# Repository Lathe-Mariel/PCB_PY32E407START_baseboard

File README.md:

KiCAD Project for Mother board of PY32E407_START(PUYA).

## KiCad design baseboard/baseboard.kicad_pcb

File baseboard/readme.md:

# BoM

型式 | 数量 | アイテム
---|---|---
FH-2x25SG(10) | 2 | 2.54連結ピンソケット
PH-2x5SG | 1 | 2.54ピンヘッダ
FH-2x2SG | 2 | 2.54ピンソケット
DTS-63-N-V-BLK | 1 | タクトスイッチ
 | 6 | Pmodソケット
OSR50603C1E | 4 | SMD LED
RC0603J220R | 4 | SMD 1608 220Ω
RK73B1JTTD103J | 4 | SMD 1608 10kΩ
TVBP06-B043CW-B | 4 | タクトスイッチ
ATA6561-GAQW-N | 1 | CANトランシーバ
SDCW3216-2-222TF | 1 | 表面実装用コモンモードチョークコイル
RC0603FR-0760R4L | 2 | SMD1608 60.4Ω
 | 1 | SMD1608 4.7nF
SM24CANB-02HTG | 1 | CAN TVS
 | 1 | CAN スクリューターミナル

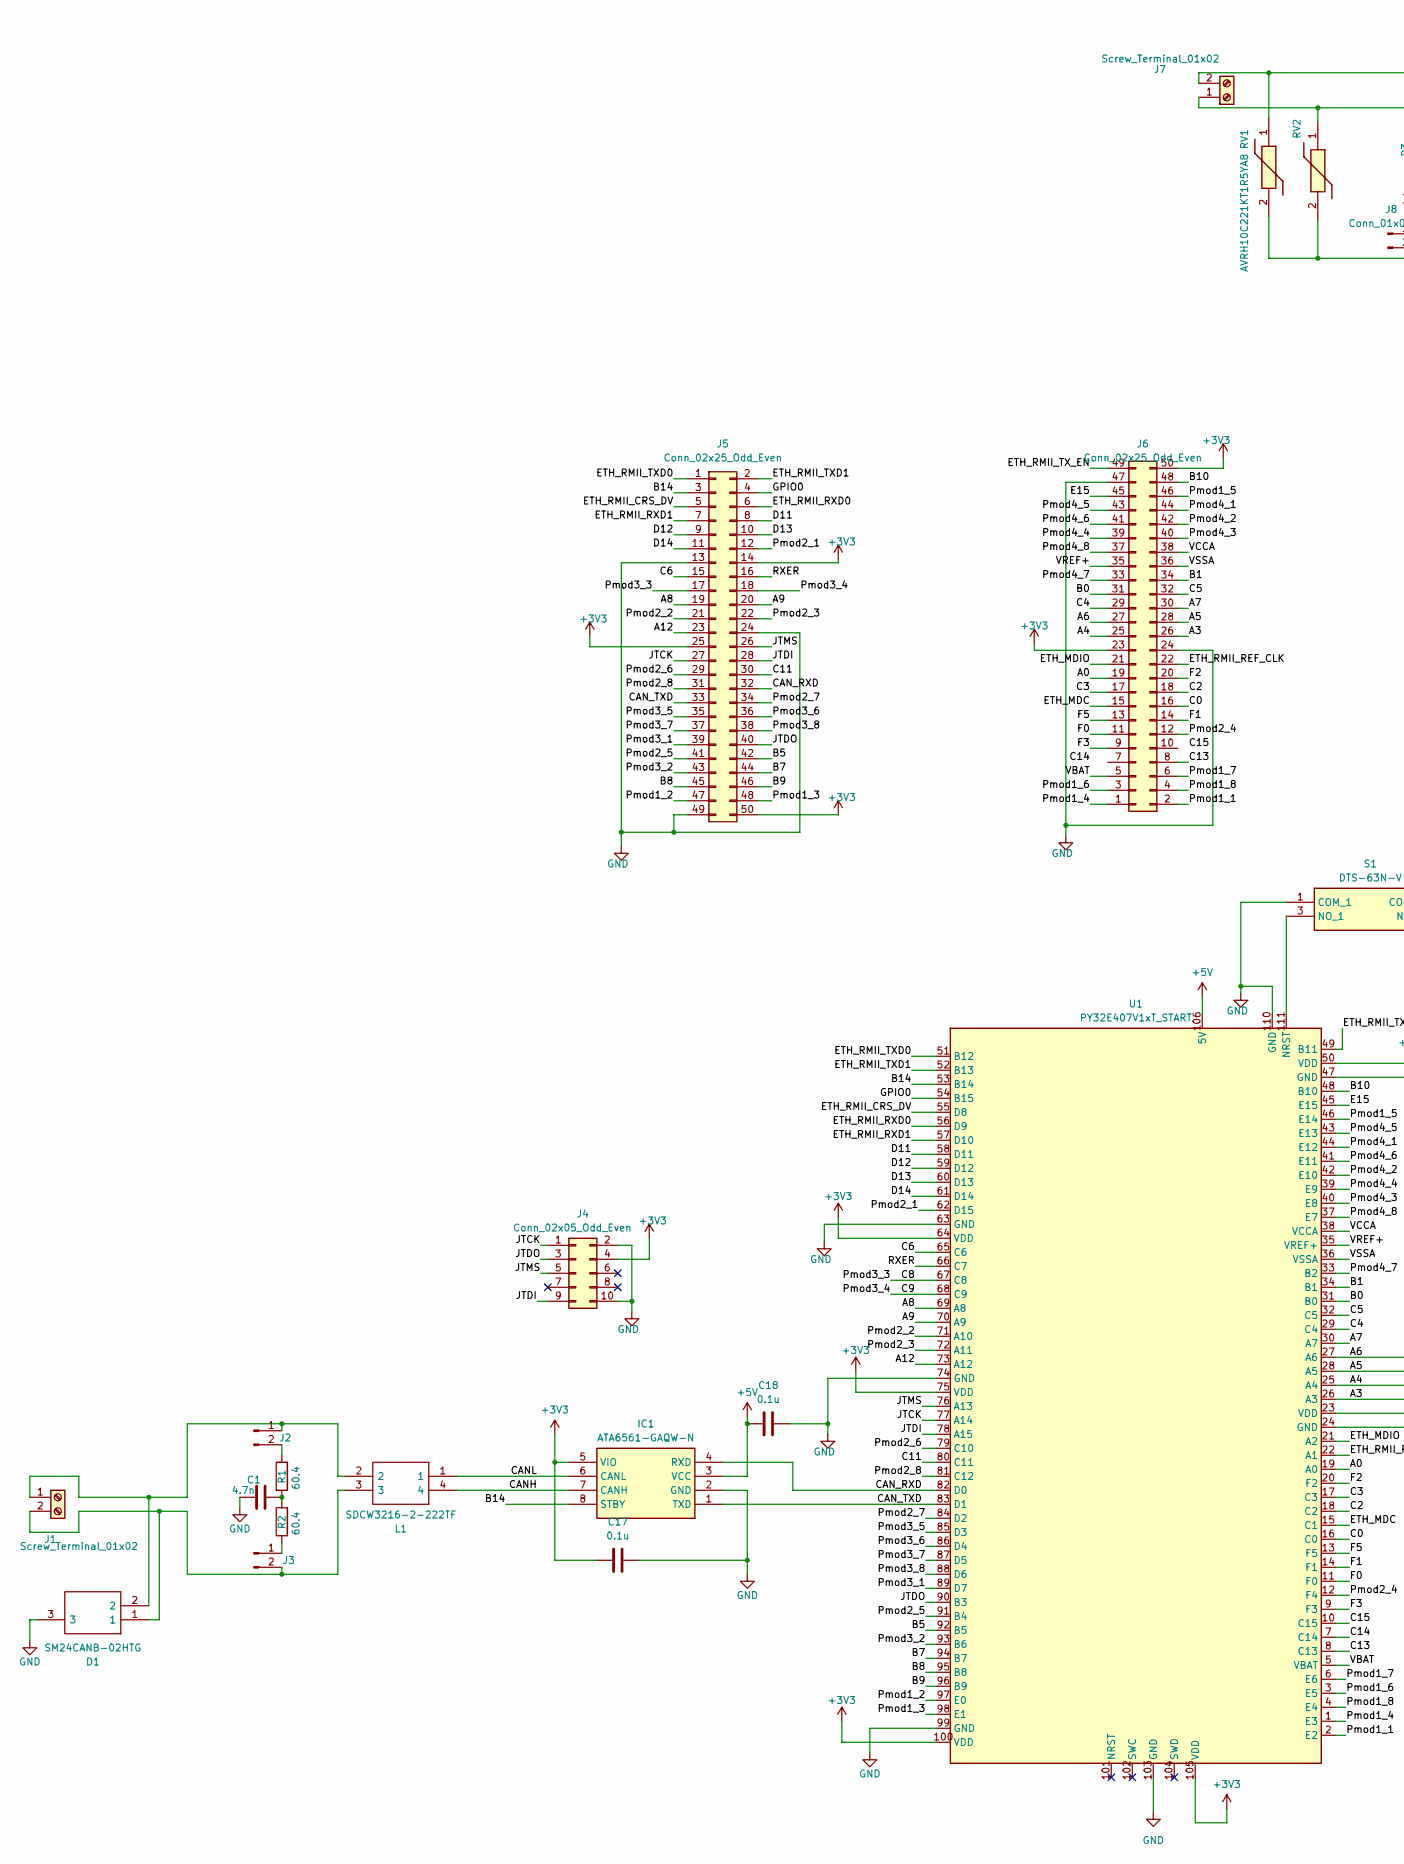
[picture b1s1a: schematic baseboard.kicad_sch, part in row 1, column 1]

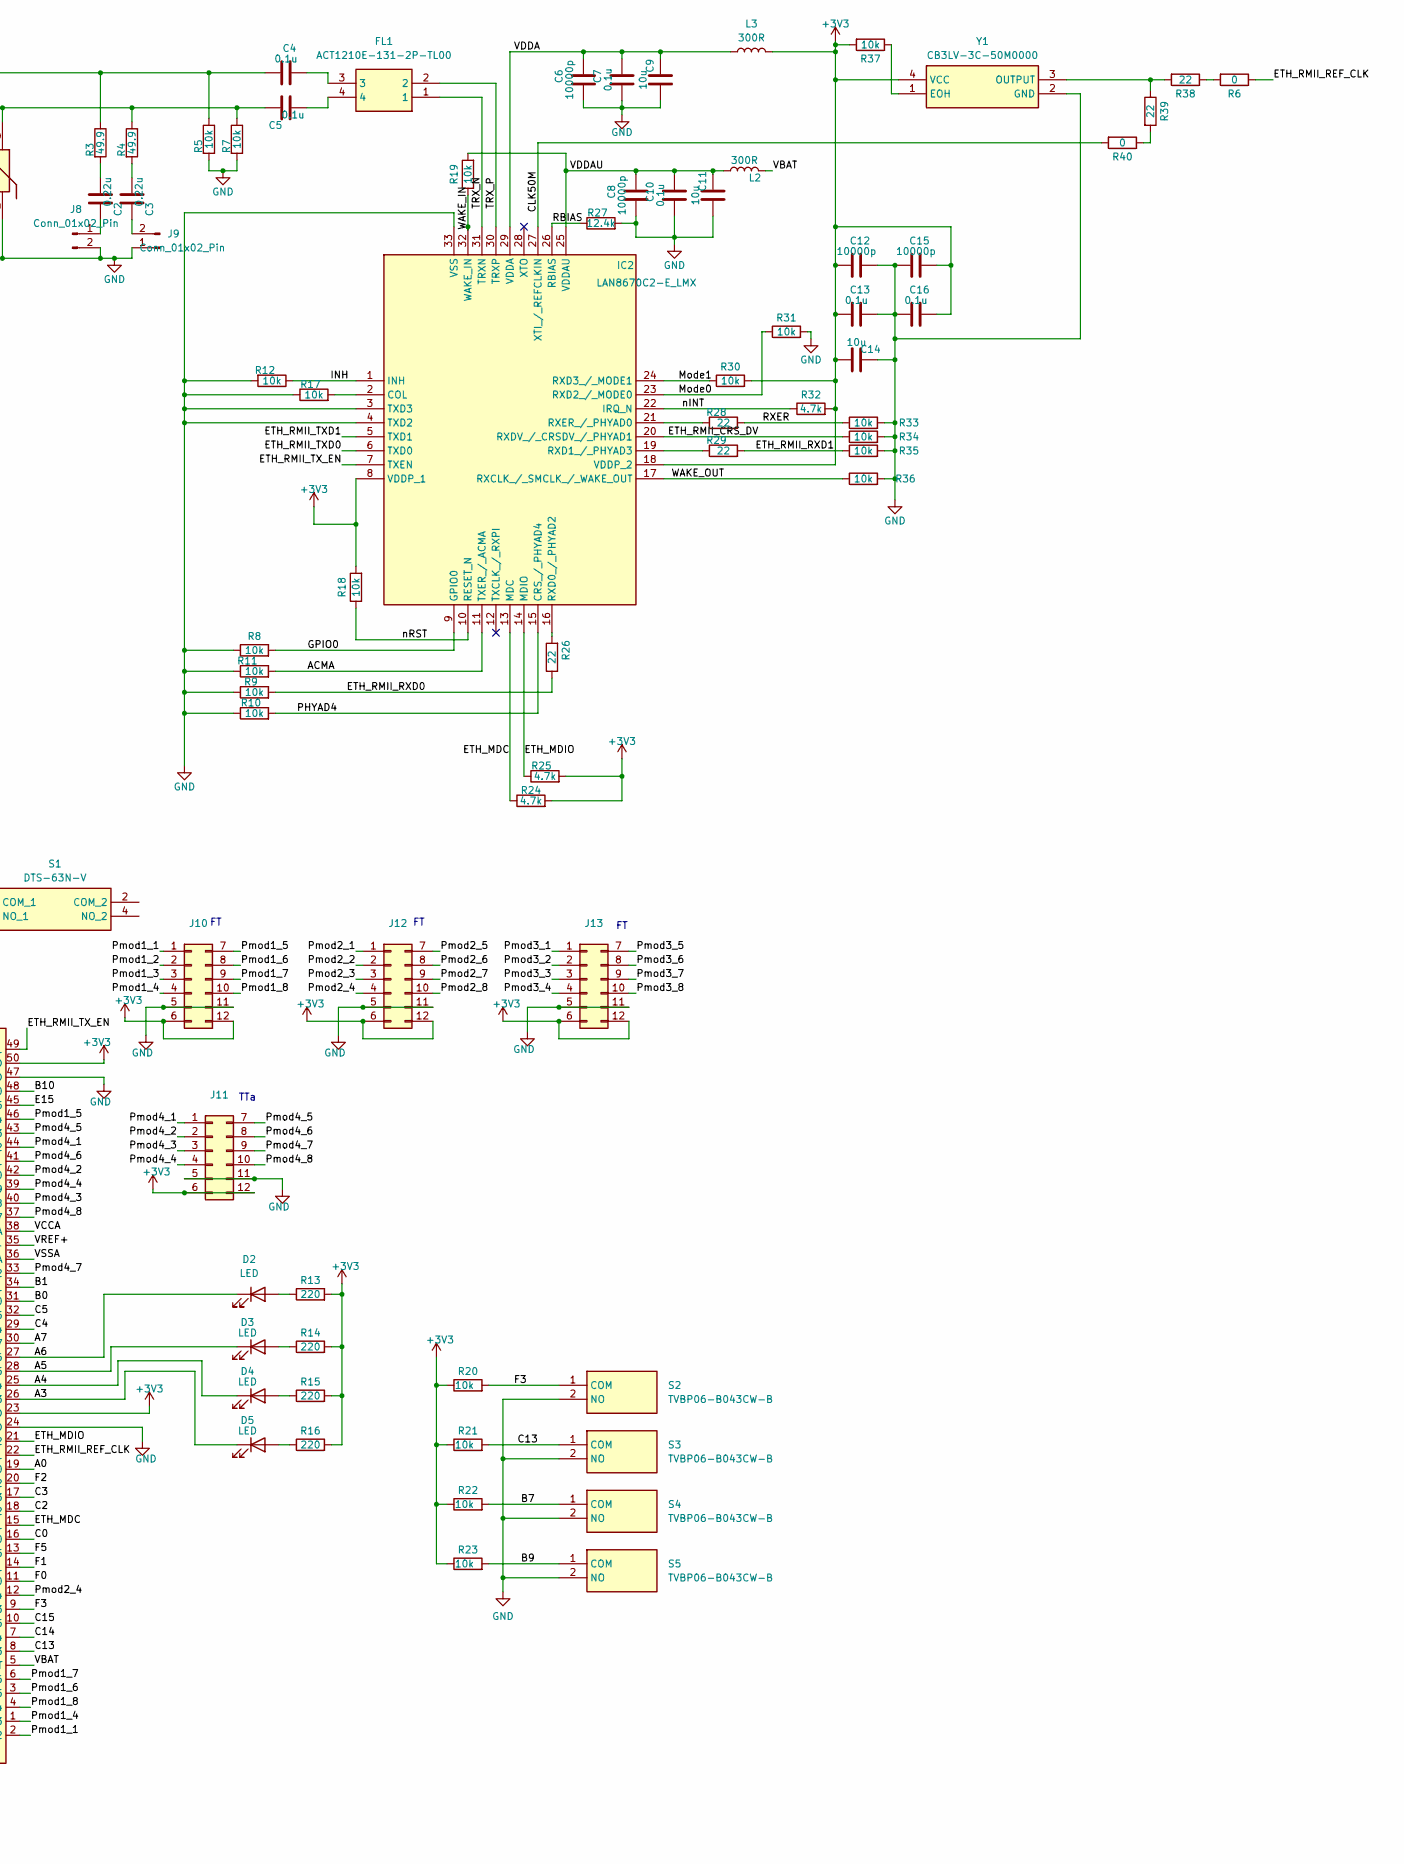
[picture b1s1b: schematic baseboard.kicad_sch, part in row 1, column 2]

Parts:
C1: 4.7n; C_0603_1608Metric_Pad1.08x0.95mm_HandSolder
C2, C3: 0.22u; C_0603_1608Metric_Pad1.08x0.95mm_HandSolder
C4, C5, C7, C10, C13, C16, C17, C18: 0.1u; C_0603_1608Metric_Pad1.08x0.95mm_HandSolder
C6, C8, C12, C15: 10000p; C_0603_1608Metric_Pad1.08x0.95mm_HandSolder
C9, C11, C14: 10u; C_0805_2012Metric_Pad1.18x1.45mm_HandSolder
D1: SM24CANB-02HTG; SM24CANB02HTG; Manufacturer_Part_Number SM24CANB-02HTG
D2, D3, D4, D5: LED; LED_0603_1608Metric_Pad1.05x0.95mm_HandSolder
FL1: ACT1210E-131-2P-TL00; ACT1210E1312PTL00; Manufacturer_Part_Number ACT1210E-131-2P-TL00
IC1: ATA6561-GAQW-N; SOIC127P600X175-8N; Manufacturer_Part_Number ATA6561-GAQW-N
IC2: LAN8670C2-E_LMX; QFN50P500X500X100-33N-D; Manufacturer_Part_Number LAN8670C2-E/LMX
J1: Screw_Terminal_01x02; TerminalBlock_Phoenix_MKDS-1,5-2-5.08_1x02_P5.08mm_Horizont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
J2, J3, J8, J9: Conn_01x02_Pin; PinHeader_1x02_P2.54mm_Vertical
J4: Conn_02x05_Odd_Even; PinHeader_2x05_P2.54mm_Vertical
J5, J6: Conn_02x25_Odd_Even; PinHeader_2x25_P2.54mm_Vertical
J7: Screw_Terminal_01x02; TerminalBlock_MetzConnect_Type055_RT01502HDWU_1x02_P5.00mm_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
J10, J11, J12, J13: Pmod_socket
L1: SDCW3216-2-222TF; SDCW32162222TF; Manufacturer_Part_Number SDCW3216-2-222TF
L2, L3: 300R; L_0603_1608Metric_Pad1.05x0.95mm_HandSolder
R1, R2: 60.4; R_0603_1608Metric_Pad0.98x0.95mm_HandSolder
R3, R4: 49.9; R_0603_1608Metric_Pad0.98x0.95mm_HandSolder
R5, R7, R8, R9, R10, R11, R12, R17, R18, R19, R20, R21, R22, R23, R30, R31, R33, R34, R35, R36, R37: 10k; R_0603_1608Metric_Pad0.98x0.95mm_HandSolder
R6, R40: 0; R_0603_1608Metric_Pad0.98x0.95mm_HandSolder
R13, R14, R15, R16: 220; R_0603_1608Metric_Pad0.98x0.95mm_HandSolder
R24, R25, R32: 4.7k; R_0603_1608Metric_Pad0.98x0.95mm_HandSolder
R26, R28, R29, R38, R39: 22; R_0603_1608Metric_Pad0.98x0.95mm_HandSolder
R27: 12.4k; R_0603_1608Metric_Pad0.98x0.95mm_HandSolder
RV1, RV2: AVRH10C221KT1R5YA8; RESC1005X55N; Manufacturer_Part_Number AVRH10C221KT1R5YA8
S1: DTS-63N-V; DTS63NV; Manufacturer_Part_Number DTS-63N-V
S2, S3, S4, S5: TVBP06-B043CW-B; TVBP06B043CWB; Manufacturer_Part_Number TVBP06-B043CW-B
U1: PY32E407V1xT_START
Y1: CB3LV-3C-50M0000; CB3LV3C50M0000; Manufacturer_Part_Number CB3LV-3C-50M0000

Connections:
+3V3: C12.1, C13.1, C14.1, C15.2, C16.2, C17.1, IC1.5 (VIO), IC2.8 (VDDP_1), IC2.18 (VDDP_2), J4.4, J5.14, J5.25, J5.50, J6.23 (Pin_24), J6.50 (Pin_49), J10.6, J10.12, J11.6, J11.12, J12.6, J12.12, J13.6, J13.12, L3.2, R13.2, R14.2, R15.2, R16.2, R18.2, R20.1, R21.1, R22.1, R23.1, R24.2, R25.2, R30.2, R32.2, R37.2, U1.23 (VDD), U1.50 (VDD), U1.64 (VDD), U1.75 (VDD), U1.100 (VDD), U1.105 (VDD), Y1.4 (VCC)
+5V: C18.1, IC1.3 (VCC), U1.106 (5V)
/A0: J6.19 (Pin_20), U1.19 (A0)
/A3: D5.1 (K), J6.26 (Pin_25), U1.26 (A3)
/A4: D4.1 (K), J6.25 (Pin_26), U1.25 (A4)
/A5: D3.1 (K), J6.28 (Pin_27), U1.28 (A5)
/A6: D2.1 (K), J6.27 (Pin_28), U1.27 (A6)
/A7: J6.30 (Pin_29), U1.30 (A7)
/A8: J5.19, U1.69 (A8)
/A9: J5.20, U1.70 (A9)
/A12: J5.23, U1.73 (A12)
/ACMA: IC2.11 (TXER_/_ACMA), R11.2
/B0: J6.31 (Pin_32), U1.31 (B0)
/B1: J6.34 (Pin_33), U1.34 (B1)
/B5: J5.42, U1.92 (B5)
/B7: J5.44, R22.2, S4.1 (COM), U1.94 (B7)
/B8: J5.45, U1.95 (B8)
/B9: J5.46, R23.2, S5.1 (COM), U1.96 (B9)
/B10: J6.48 (Pin_47), U1.48 (B10)
/B14: IC1.8 (STBY), J5.3, U1.53 (B14)
/C0: J6.16 (Pin_15), U1.16 (C0)
/C2: J6.18 (Pin_17), U1.18 (C2)
/C3: J6.17 (Pin_18), U1.17 (C3)
/C4: J6.29 (Pin_30), U1.29 (C4)
/C5: J6.32 (Pin_31), U1.32 (C5)
/C6: J5.15, U1.65 (C6)
/C8: J5.17, J13.3, U1.67 (C8)
/C9: J5.18, J13.4, U1.68 (C9)
/C11: J5.30, U1.80 (C11)
/C13: J6.8 (Pin_7), R21.2, S3.1 (COM), U1.8 (C13)
/C14: U1.7 (C14)
/C15: U1.10 (C15)
/CANH: IC1.7 (CANH), L1.4
/CANL: IC1.6 (CANL), L1.1
/CAN_RXD: IC1.4 (RXD), J5.32, U1.82 (D0)
/CAN_TXD: IC1.1 (TXD), J5.33, U1.83 (D1)
/CLK50M: IC2.27 (XTI_/_REFCLKIN), R40.2
/D11: J5.8, U1.58 (D11)
/D12: J5.9, U1.59 (D12)
/D13: J5.10, U1.60 (D13)
/D14: J5.11, U1.61 (D14)
/E15: J6.45 (Pin_46), U1.45 (E15)
/ETH_MDC: IC2.13 (MDC), J6.15 (Pin_16), R24.1, U1.15 (C1)
/ETH_MDIO: IC2.14 (MDIO), J6.21 (Pin_22), R25.1, U1.21 (A2)
/ETH_RMII_CRS_DV: IC2.20 (RXDV_/_CRSDV_/_PHYAD1), J5.5, R34.1, U1.55 (D8)
/ETH_RMII_REF_CLK: J6.22 (Pin_21), R6.1, U1.22 (A1)
/ETH_RMII_RXD0: J5.6, R9.2, R26.1, U1.56 (D9)
/ETH_RMII_RXD1: J5.7, R29.2, R35.1, U1.57 (D10)
/ETH_RMII_TXD0: IC2.6 (TXD0), J5.1, U1.51 (B12)
/ETH_RMII_TXD1: IC2.5 (TXD1), J5.2, U1.52 (B13)
/ETH_RMII_TX_EN: IC2.7 (TXEN), J6.49 (Pin_50), U1.49 (B11)
/F0: J6.11 (Pin_12), U1.11 (F0)
/F1: J6.14 (Pin_13), U1.14 (F1)
/F2: J6.20 (Pin_19), U1.20 (F2)
/F3: J6.9 (Pin_10), R20.2, S2.1 (COM), U1.9 (F3)
/F5: J6.13 (Pin_14), U1.13 (F5)
/GPIO0: IC2.9 (GPIO0), J5.4, R8.2, U1.54 (B15)
/INH: IC2.1 (INH), R12.1
/JTCK: J4.1, J5.27, U1.77 (A14)
/JTDI: J4.9, J5.28, U1.78 (A15)
/JTDO: J4.3, J5.40, U1.90 (B3)
/JTMS: J4.5, J5.26, U1.76 (A13)
/Mode0: IC2.23 (RXD2_/_MODE0), R31.1
/Mode1: IC2.24 (RXD3_/_MODE1), R30.1
/PHYAD4: IC2.15 (CRS_/_PHYAD4), R10.2
/Pmod1_1: J6.2 (Pin_1), J10.1, U1.2 (E2)
/Pmod1_2: J5.47, J10.2, U1.97 (E0)
/Pmod1_3: J5.48, J10.3, U1.98 (E1)
/Pmod1_4: J6.1 (Pin_2), J10.4, U1.1 (E3)
/Pmod1_5: J6.46 (Pin_45), J10.7, U1.46 (E14)
/Pmod1_6: J6.3 (Pin_4), J10.8, U1.3 (E5)
/Pmod1_7: J6.6 (Pin_5), J10.9, U1.6 (E6)
/Pmod1_8: J6.4 (Pin_3), J10.10, U1.4 (E4)
/Pmod2_1: J5.12, J12.1, U1.62 (D15)
/Pmod2_2: J5.21, J12.2, U1.71 (A10)
/Pmod2_3: J5.22, J12.3, U1.72 (A11)
/Pmod2_4: J6.12 (Pin_11), J12.4, U1.12 (F4)
/Pmod2_5: J5.41, J12.7, U1.91 (B4)
/Pmod2_6: J5.29, J12.8, U1.79 (C10)
/Pmod2_7: J5.34, J12.9, U1.84 (D2)
/Pmod2_8: J5.31, J12.10, U1.81 (C12)
/Pmod3_1: J5.39, J13.1, U1.89 (D7)
/Pmod3_2: J5.43, J13.2, U1.93 (B6)
/Pmod3_5: J5.35, J13.7, U1.85 (D3)
/Pmod3_6: J5.36, J13.8, U1.86 (D4)
/Pmod3_7: J5.37, J13.9, U1.87 (D5)
/Pmod3_8: J5.38, J13.10, U1.88 (D6)
/Pmod4_1: J6.44 (Pin_43), J11.1, U1.44 (E12)
/Pmod4_2: J6.42 (Pin_41), J11.2, U1.42 (E10)
/Pmod4_3: J6.40 (Pin_39), J11.3, U1.40 (E8)
/Pmod4_4: J6.39 (Pin_40), J11.4, U1.39 (E9)
/Pmod4_5: J6.43 (Pin_44), J11.7, U1.43 (E13)
/Pmod4_6: J6.41 (Pin_42), J11.8, U1.41 (E11)
/Pmod4_7: J6.33 (Pin_34), J11.9, U1.33 (B2)
/Pmod4_8: J6.37 (Pin_38), J11.10, U1.37 (E7)
/RBIAS: IC2.26 (RBIAS), R27.1
/RXER: J5.16, R28.2, R33.1, U1.66 (C7)
/TRX_N: FL1.1, IC2.31 (TRXN)
/TRX_P: FL1.2, IC2.30 (TRXP)
/VBAT: J6.5 (Pin_6), L2.2, U1.5 (VBAT)
/VCCA: J6.38 (Pin_37), U1.38 (VCCA)
/VDDA: C6.2, C7.2, C9.2, IC2.29 (VDDA), L3.1
/VDDAU: C8.2, C10.2, C11.2, IC2.25 (VDDAU), L2.1, R19.2
/VREF+: J6.35 (Pin_36), U1.35 (VREF+)
/VSSA: J6.36 (Pin_35), U1.36 (VSSA)
/WAKE_IN: IC2.32 (WAKE_IN), R19.1
/WAKE_OUT: IC2.17 (RXCLK_/_SMCLK_/_WAKE_OUT), R36.1
/nINT: IC2.22 (IRQ_N), R32.1
/nRST: IC2.10 (RESET_N), R18.1
GND: C1.2, C6.1, C7.1, C8.1, C9.1, C10.1, C11.1, C12.2, C13.2, C14.2, C15.1, C16.1, C17.2, C18.2, D1.3, IC1.2 (GND), IC2.3 (TXD3), IC2.4 (TXD2), IC2.33 (VSS), J4.2, J4.10, J5.13, J5.24, J5.49, J6.24 (Pin_23), J6.47 (Pin_48), J8.2, J9.1, J10.5, J10.11, J11.5, J11.11, J12.5, J12.11, J13.5, J13.11, R5.2, R7.2, R8.1, R9.1, R10.1, R11.1, R12.2, R17.1, R27.2, R31.2, R33.2, R34.2, R35.2, R36.2, RV1.2, RV2.2, S1.1 (COM_1), S2.2 (NO), S3.2 (NO), S4.2 (NO), S5.2 (NO), U1.24 (GND), U1.47 (GND), U1.63 (GND), U1.74 (GND), U1.99 (GND), U1.103 (GND), U1.110 (GND), Y1.2 (GND)
unnamed: C1.1, R1.1, R2.2
unnamed: C2.2, R3.2
unnamed: C3.2, R4.2
unnamed: C4.2, FL1.3
unnamed: C5.2, FL1.4
unnamed: D2.2 (A), R13.1
unnamed: D3.2 (A), R14.1
unnamed: D4.2 (A), R15.1
unnamed: D5.2 (A), R16.1
unnamed: IC2.2 (COL), R17.2
unnamed: IC2.16 (RXD0_/_PHYAD2), R26.2
unnamed: IC2.19 (RXD1_/_PHYAD3), R29.1
unnamed: IC2.21 (RXER_/_PHYAD0), R28.1
unnamed: D1.2, J1.1, J2.1, L1.2
unnamed: D1.1, J1.2, J3.2, L1.3
unnamed: J2.2, R1.2
unnamed: J3.1, R2.1
unnamed: C5.1, J7.1, R4.1, R7.1, RV2.1
unnamed: C4.1, J7.2, R3.1, R5.1, RV1.1
unnamed: C2.1, J8.1
unnamed: C3.1, J9.2
unnamed: R6.2, R38.1
unnamed: R39.2, R40.1
unnamed: S1.3 (NO_1), U1.111 (NRST)
unnamed: R37.1, Y1.1 (EOH)
unnamed: R38.2, R39.1, Y1.3 (OUTPUT)

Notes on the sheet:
TTa

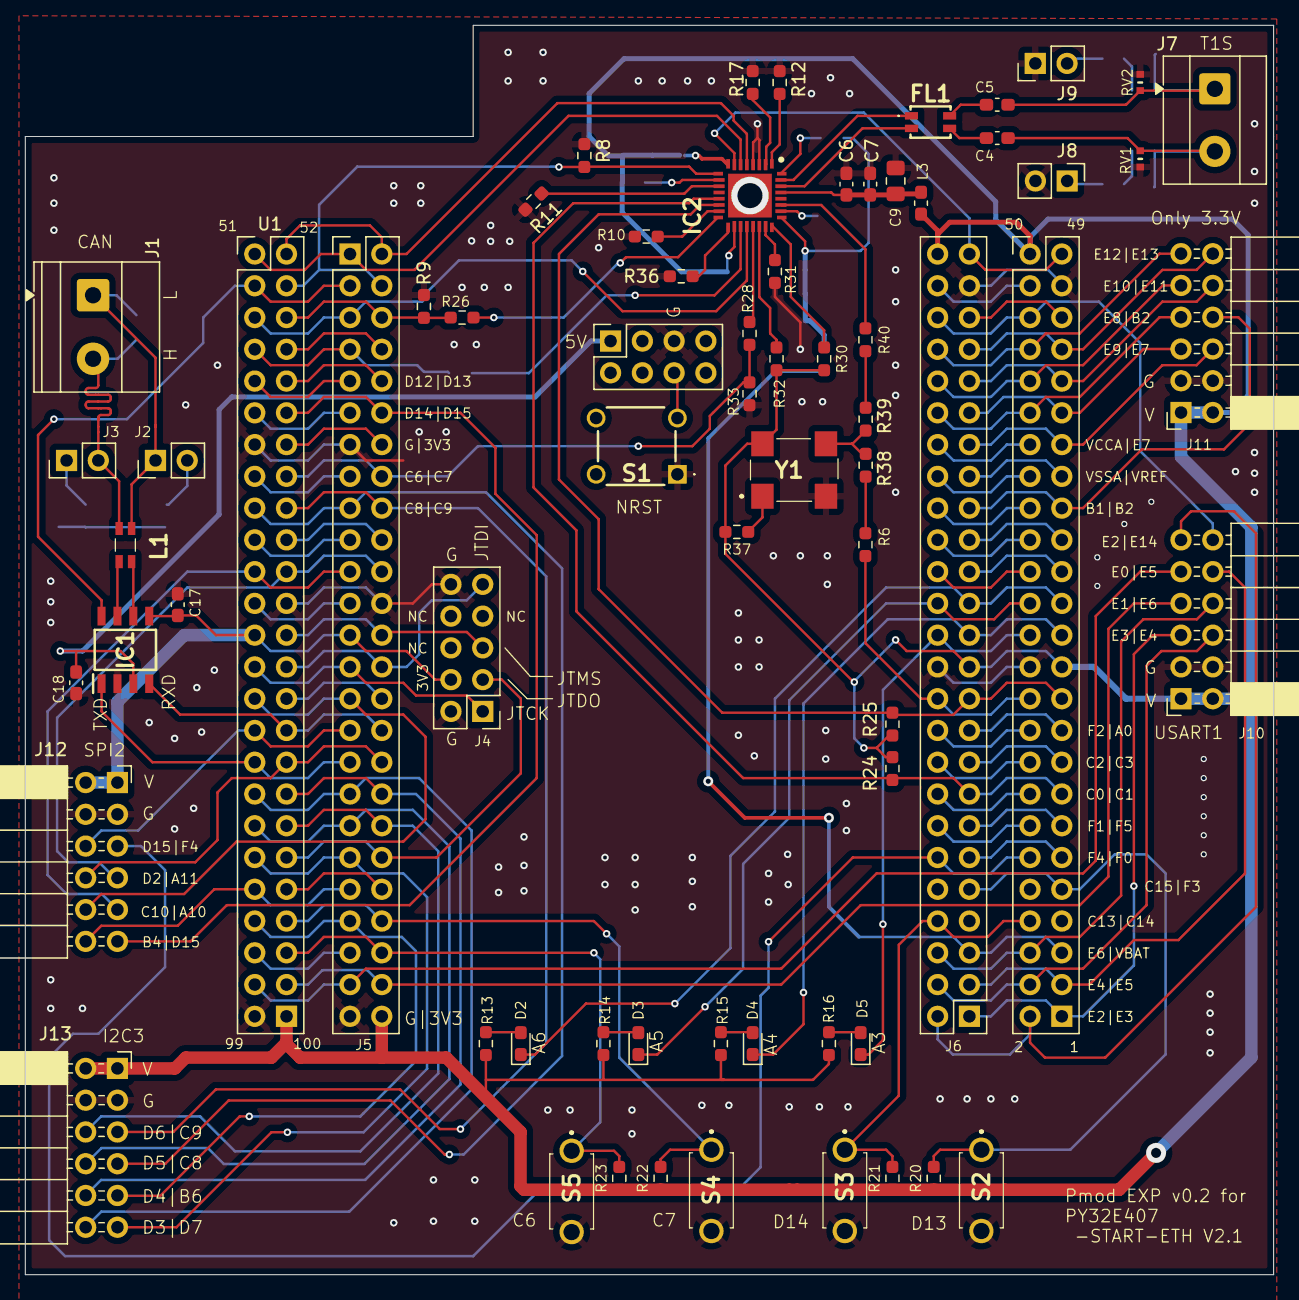
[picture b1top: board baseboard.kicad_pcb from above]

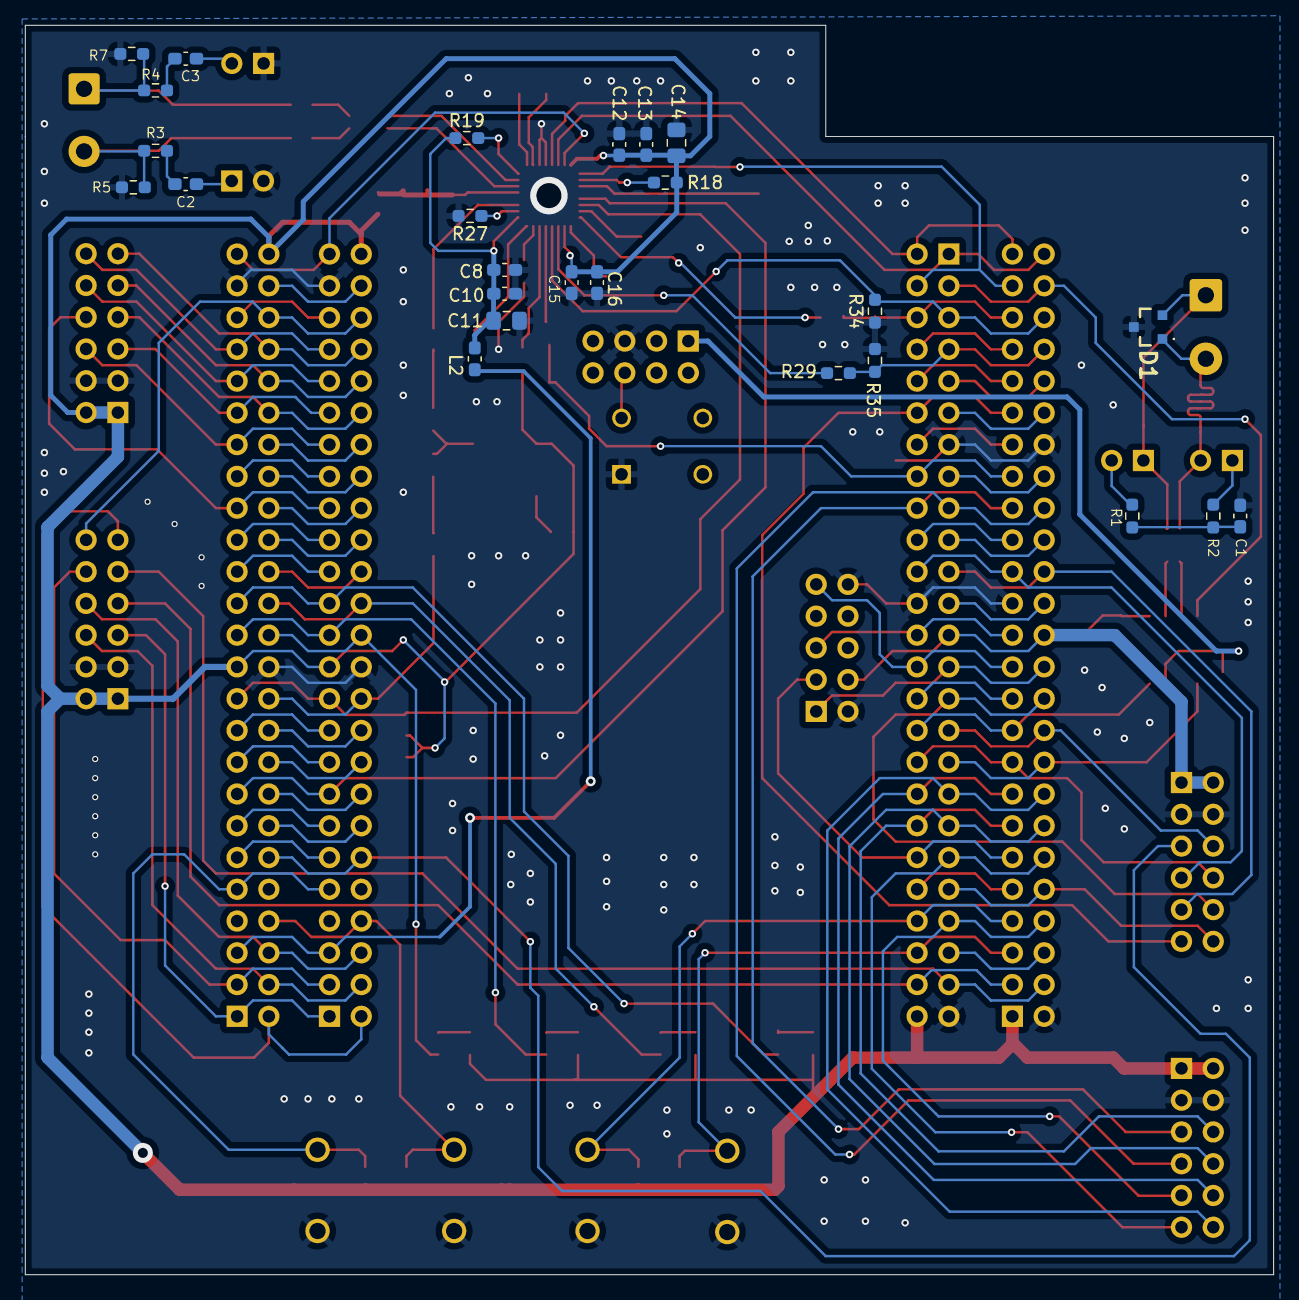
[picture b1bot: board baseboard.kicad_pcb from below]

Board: 2 copper layers, 99.8 x 99.9 mm, 91 parts (25 on the bottom side), 134 nets.

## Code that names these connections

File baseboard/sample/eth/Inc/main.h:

/**
  ******************************************************************************
  * @file    main.h
  * @author  MCU Application Team
  * @brief   Header for main.c file.
  *          LAN8670 10BASE-T1S (RMII) bring-up on the PY32E407 baseboard.
  ******************************************************************************
  * @attention
  *
  * <h2><center>&copy; Copyright (c) 2023 Puya Semiconductor Co.
  * All rights reserved.</center></h2>
  *
  * This software component is licensed by Puya under BSD 3-Clause license,
  * the "License"; You may not use this file except in compliance with the
  * License. You may obtain a copy of the License at:
  *                        opensource.org/licenses/BSD-3-Clause
  *
  ******************************************************************************
  */

/* Define to prevent recursive inclusion -------------------------------------*/
#ifndef __MAIN_H
#define __MAIN_H

#ifdef __cplusplus
extern "C" {
#endif

/* Includes ------------------------------------------------------------------*/
#include "py32e4xx_hal.h"
#include "py32e407xx_Start_Kit.h"

/* Private defines -----------------------------------------------------------*/

/*
 * LAN8670 10BASE-T1S PHY (IC2) on the baseboard.
 * It is wired to the ETH RMII pin set, which is fixed on this device:
 *
 *   PB11 ------> ETH_TX_EN
 *   PB12 ------> ETH_TXD0
 *   PB13 ------> ETH_TXD1
 *   PC4  ------> ETH_RXD0
 *   PC5  ------> ETH_RXD1
 *   PD8  ------> ETH_CRS_DV
 *   PC1  ------> ETH_MDC
 *   PA2  ------> ETH_MDIO
 *   PA1  <----- ETH_REF_CLK   (50 MHz from the on-board CB3LV oscillator)
 *
 * LAN8670 strap pins on this board:
 *   MODE0 = 0, MODE1 = 1  -> MODE[1:0] = 10b -> RMII with 50 MHz REFCLKIN
 *   PHYAD[4:0] all pulled low -> PHY address 0
 *   INH/ACMA/GPIO0/nINT/nRST are pulled by 10k resistors.
 */
#define ETH_GPIO_PORT_TX              GPIOB
#define ETH_GPIO_PORT_RX              GPIOC
#define ETH_GPIO_PORT_CRS             GPIOD
#define ETH_GPIO_PORT_MDIO            GPIOA

#define ETH_TX_EN_PIN                 GPIO_PIN_11
#define ETH_TXD0_PIN                  GPIO_PIN_12
#define ETH_TXD1_PIN                  GPIO_PIN_13
#define ETH_RXD0_PIN                  GPIO_PIN_4
#define ETH_RXD1_PIN                  GPIO_PIN_5
#define ETH_CRS_DV_PIN                GPIO_PIN_8
#define ETH_MDC_PIN                   GPIO_PIN_1
#define ETH_MDIO_PIN                  GPIO_PIN_2
#define ETH_REF_CLK_PIN               GPIO_PIN_1

#define ETH_GPIO_AF                   GPIO_AF13_ETH

/* PHY address, PHYAD[4:0] = 0 on this baseboard */
#define LAN8670_PHY_ADDR              0U

/* 10BASE-T1S runs at 10 Mbit/s, full duplex */
#define LAN8670_ETH_SPEED             ETH_SPEED_10M
#define LAN8670_ETH_DUPLEX            ETH_MODE_FULLDUPLEX

/* Number of DMA descriptors, keep in sync with py32e407_hal_conf.h */
#define ETH_RX_DESC_CNT               4U
#define ETH_TX_DESC_CNT               4U

/* Interrupt priority for the ETH global interrupt */
#define ETH_IT_PRIORITY               3U

/* USART1 (PY-LINK virtual COM port) used for the diagnostic console */
#define CONSOLE_UART                  USART1
#define CONSOLE_UART_BAUDRATE         921600U
#define CONSOLE_UART_TX_PIN           GPIO_PIN_9
#define CONSOLE_UART_RX_PIN           GPIO_PIN_10
#define CONSOLE_UART_GPIO_PORT        GPIOA
#define CONSOLE_UART_GPIO_AF          GPIO_AF7_USART1
#define CONSOLE_UART_GPIO_CLK_ENABLE() __HAL_RCC_GPIOA_CLK_ENABLE()
#define CONSOLE_UART_IT_PRIORITY      2U

/* On-board LEDs (active low).
   Board silk order is D5=PA3, D4=PA4, D3=PA5, D2=PA6, so the schematic
   reference and the port bit run in opposite directions.  The macros below
   keep the application naming (LED_D1..LED_D4 in port order PA3..PA6). */
#define LED_D1_PIN                    GPIO_PIN_3   /* PA3 : board D5, MAC init failure */
#define LED_D2_PIN                    GPIO_PIN_4   /* PA4 : board D4, frames received  */
#define LED_D3_PIN                    GPIO_PIN_5   /* PA5 : board D3, frames sent      */
#define LED_D4_PIN                    GPIO_PIN_6   /* PA6 : board D2, demo TX blink    */
#define LED_PORT                      GPIOA
#define LED_ALL_PINS                  (LED_D1_PIN | LED_D2_PIN | LED_D3_PIN | LED_D4_PIN)
#define LED_GPIO_CLK_ENABLE()         __HAL_RCC_GPIOA_CLK_ENABLE()

/* EtherType used by the PHY bring-up demo frames */
#define DEMO_ETHERTYPE                0x88B5U

/* Exported variables --------------------------------------------------------*/
extern ETH_HandleTypeDef heth;

/* Exported functions prototypes ---------------------------------------------*/
void APP_ErrorHandler(void);

/* Diagnostic console -------------------------------------------------------*/
void Console_Init(void);
void Console_Write(const char *Str);
void Console_Printf(const char *Fmt, ...);
extern SCI_HandleTypeDef hConsoleUart;

#ifdef __cplusplus
}
#endif

#endif /* __MAIN_H */

/************************ (C) COPYRIGHT Puya *****END OF FILE******************/

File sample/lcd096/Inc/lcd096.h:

/**
  ******************************************************************************
  * @file    lcd096.h
  * @brief   Software (bit-bang) SPI driver for the Pmod-LCD-0.96 v1.0 module
  *          (160x80 RGB565, ST7735S controller).
  *
  *          The module's 12-pin Pmod header only carries
  *            CS, MOSI(SDA), DC(RS), CLK(SCL), GND, VCC
  *          on its signal row; RESET sits on the opposite row, in the position
  *          directly opposite DC (see LCD096_PMOD_ROW below).
  ******************************************************************************
  */

#ifndef __LCD096_H
#define __LCD096_H

#ifdef __cplusplus
extern "C" {
#endif

#include "py32e4xx_hal.h"

/* Panel geometry (native portrait orientation of the ST7735S panel). */
#define LCD096_WIDTH          160U
#define LCD096_HEIGHT         80U

/* Full ST7735S frame memory size (GM[1:0] = "00" -> 132 x 162). The fill uses
   this so a solid colour is independent of the glass offset / addressing mode.

   NOTE: the driver uses COLMOD = 0x05, which is the ST7735S's 18-bit (RGB666)
   interface, so each pixel is THREE bytes on the wire even though the API takes
   a 16-bit RGB565 value (the byte split is done in LCD096_WritePixel()). That is
   what the module's own reference firmware does, and a logic capture of the bus
   confirms 3 bytes/pixel, so it is intentional. */
#define LCD096_FRAME_W        132U
#define LCD096_FRAME_H        162U

/* -------------------------------------------------------------------------- */
/* Pin map                                                                    */
/* -------------------------------------------------------------------------- */
/*
   A Pmod module can be plugged into a Pmod socket EITHER WAY ROUND, and both
   insertions are electrically valid. This driver therefore selects the mapping
   with LCD096_PMOD_ROW (or LCD096_SetPmodRow() at runtime) instead of
   hard-coding one of them.

   Base board Pmod socket J3 (silkscreen "I2C3"), pad -> net -> MCU:
     row 1 : pin1 /Pmod3_1=PD7, pin2 /Pmod3_2=PB6, pin3 /C8=PC8,
             pin4 /C9    =PC9, pin5 GND,          pin6 +3V3
     row 2 : pin7 /Pmod3_5=PD3, pin8 /Pmod3_6=PD5, pin9 /Pmod3_7=PD6,
             pin10 /Pmod3_8=PD4, pin11 GND,         pin12 +3V3

   Pmod-LCD-0.96 module header J2 (2x6 Pmod, pins 1-6 one row / 7-12 the other):
     pin 1,2,3          = NC, NC, NC
     pin 4,5,6          = RESET, GND, VCC
     pin 7,8,9,10,11,12 = VCC, GND, CLK, DC, MOSI, CS
   So the module's signal row is CS, MOSI, DC, CLK, GND, VCC and its RESET is
   on the OTHER row, directly OPPOSITE DC (not opposite CLK).

   Base board J3 pads are paired (1,7)(2,8)(3,9)(4,10)(5,11)(6,12). Putting the
   module's signal row on J3 row 1 gives CS=PD7 MOSI=PB6 DC=PC8 CLK=PC9, and
   RESET then sits on the module's pin 4 -> J3 pin 9 -> PD6. That is the
   insertion the base board silkscreen labels describe.

   Row 1 insertion (default, matches the base board silkscreen labels)
     CS   -> J3 pin1  = PD7
     MOSI -> J3 pin2  = PB6
     DC   -> J3 pin3  = PC8
     CLK  -> J3 pin4  = PC9
     RST  -> J3 pin9  = PD6      <-- NOT PD4!
   Row 2 insertion (module rotated 180 deg)
     CS   -> J3 pin7  = PD3
     MOSI -> J3 pin8  = PD5
     DC   -> J3 pin9  = PD6
     CLK  -> J3 pin10 = PD4
     RST  -> J3 pin3  = PC8

   NOTE: J3 pin10 (PD4) is NOT the module's RESET. In BOTH insertions it lines
   up with the module's pin 3, which is unused. Driving it changes nothing.
*/
/* Row 1 insertion (default): CS=PD7, MOSI=PB6, DC=PC8, CLK=PC9, RESET=PD6. */
#define LCD096_R1_CS_PORT     GPIOD
#define LCD096_R1_CS_PIN      GPIO_PIN_7      /* J3 pin1  */
#define LCD096_R1_SDA_PORT    GPIOB
#define LCD096_R1_SDA_PIN     GPIO_PIN_6      /* J3 pin2  */
#define LCD096_R1_DC_PORT     GPIOC
#define LCD096_R1_DC_PIN      GPIO_PIN_8      /* J3 pin3  */
#define LCD096_R1_SCK_PORT    GPIOC
#define LCD096_R1_SCK_PIN     GPIO_PIN_9      /* J3 pin4  */
#define LCD096_R1_RST_PORT    GPIOD
#define LCD096_R1_RST_PIN     GPIO_PIN_6      /* J3 pin9  */

/* Row 2 insertion (module rotated 180 deg): CS=PD3, MOSI=PD5, DC=PD6,
   CLK=PD4, RESET=PC8. */
#define LCD096_R2_CS_PORT     GPIOD
#define LCD096_R2_CS_PIN      GPIO_PIN_3      /* J3 pin7  */
#define LCD096_R2_SDA_PORT    GPIOD
#define LCD096_R2_SDA_PIN     GPIO_PIN_5      /* J3 pin8  */
#define LCD096_R2_DC_PORT     GPIOD
#define LCD096_R2_DC_PIN      GPIO_PIN_6      /* J3 pin9  */
#define LCD096_R2_SCK_PORT    GPIOD
#define LCD096_R2_SCK_PIN     GPIO_PIN_4      /* J3 pin10 */
#define LCD096_R2_RST_PORT    GPIOC
#define LCD096_R2_RST_PIN     GPIO_PIN_8      /* J3 pin3  */

/* Insertion used by LCD096_Init() unless LCD096_SetPmodRow() says otherwise.
   Row 2 = CS=PD3 MOSI=PD5 DC=PD6 CLK=PD4 RST=PC8. */
#ifndef LCD096_PMOD_ROW
#define LCD096_PMOD_ROW       2U
#endif


/* -------------------------------------------------------------------------- */
/* Panel tuning                                                               */
/* -------------------------------------------------------------------------- */
/* MADCTL (0x36): 0x00 = no mirror / RGB order. Some 0.96" ST7735S panels need
   0xA0 (mirror X+Y) or 0xC0 (mirror Y) to show the visible 160x80 window in the
   right place. Harmless for a solid fill, matters for text / images. */
#ifndef LCD096_MADCTL_VALUE
#define LCD096_MADCTL_VALUE   0x00U
#endif

/* Display inversion. 0 = INVOFF (0x20), 1 = INVON (0x21). Colour-inverted
   panels (common on the small IPS-like modules) need 1; without it a white fill
   shows up black. */
#ifndef LCD096_USE_INVON
#define LCD096_USE_INVON      1
#endif

/* -------------------------------------------------------------------------- */
/* Common colours (RGB565)                                                    */
/* -------------------------------------------------------------------------- */
#define LCD096_BLACK          0x0000U
#define LCD096_WHITE          0xFFFFU
#define LCD096_RED            0xF800U
#define LCD096_GREEN          0x07E0U
#define LCD096_BLUE           0x001FU
#define LCD096_ORANGE         0xFC00U
#define LCD096_YELLOW         0xFFE0U
#define LCD096_CYAN           0x07FFU
#define LCD096_MAGENTA        0xF81FU

/* -------------------------------------------------------------------------- */
/* API                                                                        */
/* -------------------------------------------------------------------------- */

/**
  * @brief  Select which Pmod insertion the driver talks to.
  * @param  row 1 = CS=PD7/MOSI=PB6/DC=PC8/CLK=PC9/RST=PD4 (the default),
  *             2 = CS=PD3/MOSI=PD5/DC=PD6/CLK=PD4/RST=PC9 (module rotated).
  * @note   Call LCD096_Init() (and re-fill) after switching.
  */
void LCD096_SetPmodRow(uint8_t row);

/**
  * @brief  Initialise the LCD (GPIO + ST7735S power-on sequence).
  * @note   Leaves the panel display-on with the frame memory containing
  *         undefined data. Call LCD096_FillScreen() afterwards.
  */
void LCD096_Init(void);

/**
  * @brief  Bring-up aid: configure the five LCD GPIOs and drive them HIGH one at
  *         a time, so each pin can be checked with a meter/LED without a scope.
  * @param  hold_ms how long each pin stays HIGH (and the others stay LOW).
  * @note   Reports the pin under test through LCD096_DebugHook() as stage
  *         81=CS, 82=SDA(MOSI), 83=DC, 84=SCK, 85=RST. Leaves the bus in its
  *         idle state (CS high, SCK/SDA low, DC high, RST high) when done.
  */
void LCD096_PinSelfTest(uint32_t hold_ms);

/**
  * @brief  Fill the whole panel with a single RGB565 colour.
  * @param  color RGB565 colour value.
  */
void LCD096_FillScreen(uint16_t color);

/**
  * @brief  Fill an axis aligned rectangle with a single RGB565 colour.
  * @param  x,y   Top-left corner (0-based).
  * @param  w,h   Width / height in pixels (must be >= 1).
  * @param  color RGB565 colour value.
  */
void LCD096_FillRect(uint16_t x, uint16_t y, uint16_t w, uint16_t h, uint16_t color);

/**
  * @brief  Blit an RGB565 bitmap into a (x,y)-(x+w-1,y+h-1) window.
  * @param  pixels Row-major RGB565 pixel array, w*h entries.
  */
void LCD096_DrawImage(uint16_t x, uint16_t y, uint16_t w, uint16_t h,
                      const uint16_t *pixels);

#ifdef __cplusplus
}
#endif

#endif /* __LCD096_H */

/************************ (C) COPYRIGHT Puya *****END OF FILE******************/
